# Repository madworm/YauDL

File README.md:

YauDL
=====

LAYOUT FILES: (Y)et (a)nother (u)seless (D)ummy (L)oad

For testing various projects I desire an adjustable constant current sink.
Nothing fancy, not microcontroller controlled, not 'constant power', maybe
with a display, maybe just use a DMM for that. BUT I need AMPS!
I'm shooting for a device that is capable to sink 5A. At least for a limited
amount of time, a couple of minutes should be enough to see if the DUT
overheats and/or craps out.

It will be as simple as can be: MOSFET(s), heatsink, sense resistor(s),
opamp(s), gain control, reference voltage, multi-turn pot to set the
reference current. It may or may not come with binding posts.

The first opamp will amplify the voltage drop on the mOhm range sense resistor
to a useful value (1V --> 1A), the second opamp will be wired in the usual
follower setup driving the MOSFET(s). I don't want to use a 1R sense resistor,
as this causes the device to need at least 5V for 5A. I'm aiming at something
lower.

BTW. It is strictly for DC input voltages.

---

Before having PC-boards made, please make sure you know about your manufacturer's peculiarities!
Especially drill-sizes and their tolerances may vary too much and give you trouble.

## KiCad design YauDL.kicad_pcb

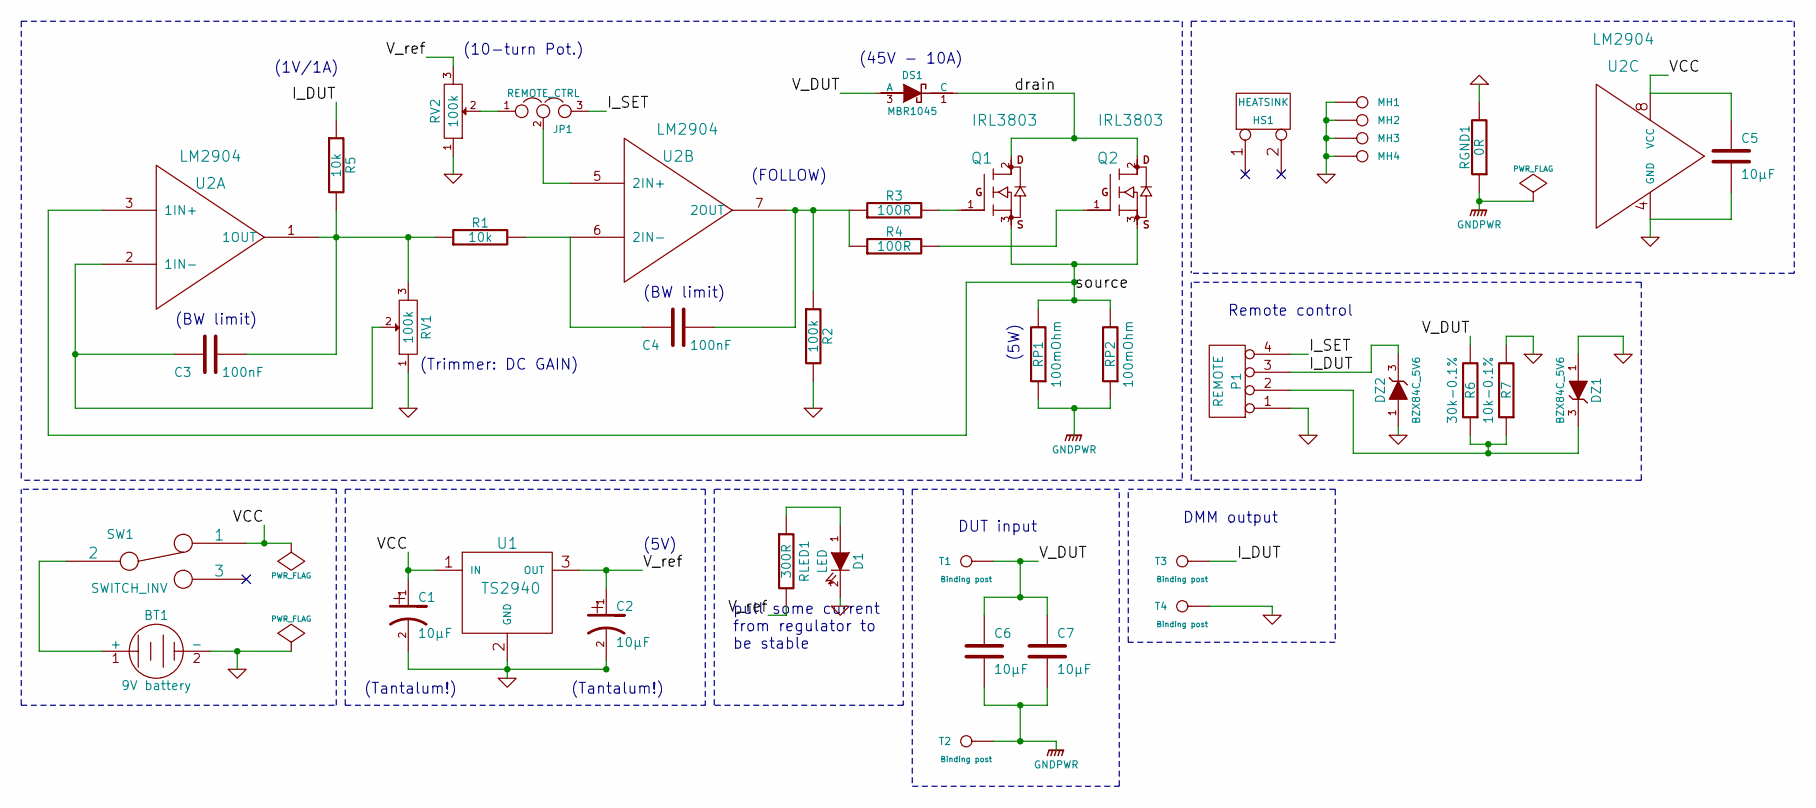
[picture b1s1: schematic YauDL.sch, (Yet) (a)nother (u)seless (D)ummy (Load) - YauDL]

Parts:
BT1: 9V battery
C1, C2, C5, C6, C7: 10µF
C3, C4: 100nF
D1: LED
DS1: MBR1045
DZ1, DZ2: BZX84C_5V6
HS1: HEATSINK
JP1: REMOTE_CTRL
MH1, MH2, MH3, MH4: CONN_1
P1: REMOTE
Q1, Q2: IRL3803
R1, R5: 10k
R2: 100k
R3, R4: 100R
R6: 30k-0.1%
R7: 10k-0.1%
RGND1: 0R
RLED1: 300R
RP1, RP2: 100mOhm
RV1, RV2: 100k
SW1: SWITCH_INV
T1, T2, T3, T4: Binding post
U1: TS2940
U2: LM2904

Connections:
/I_DUT: DZ2.3, P1.3, R5.1, T3.1
/I_SET: JP1.3, P1.4
/VCC: C1.1, C5.1, SW1.1, U1.1 (IN), U2.8 (VCC)
/V_DUT: C6.1, C7.1, DS1.3 (A), R6.2, T1.1
/V_ref: C2.1, RLED1.2, RV2.3, U1.3 (OUT)
/drain: DS1.1 (C), Q1.2 (D), Q2.2 (D)
/source: Q1.3 (S), Q2.3 (S), RP1.2, RP2.2, U2.3 (1IN+)
GND: BT1.2 (-), C1.2, C2.2, C5.2, D1.2 (K), DZ1.1, DZ2.1, MH1.1, MH2.1, MH3.1, MH4.1, P1.1, R2.2, R7.2, RGND1.2, RV1.1, RV2.1, T4.1, U1.2 (GND), U2.4 (GND)
GNDPWR: C6.2, C7.2, RGND1.1, RP1.1, RP2.1, T2.1
unnamed: D1.1 (A), RLED1.1
unnamed: C4.2, R2.1, R3.1, R4.1, U2.7 (2OUT)
unnamed: Q1.1 (G), R3.2
unnamed: C3.2, R1.1, R5.2, RV1.3, U2.1 (1OUT)
unnamed: C4.1, R1.2, U2.6 (2IN-)
unnamed: JP1.2, U2.5 (2IN+)
unnamed: BT1.1 (+), SW1.2
unnamed: JP1.1, RV2.2
unnamed: Q2.1 (G), R4.2
unnamed: DZ1.3, P1.2, R6.1, R7.1
unnamed: C3.1, RV1.2, U2.2 (1IN-)

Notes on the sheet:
Remote control
(45V - 10A)
pull some current from regulator to be stable
(Tantalum!)
(BW limit)
(5W)
DMM output
(10-turn Pot.)
(5V)
(FOLLOW)
(Trimmer: DC GAIN)
(1V/1A)
DUT input

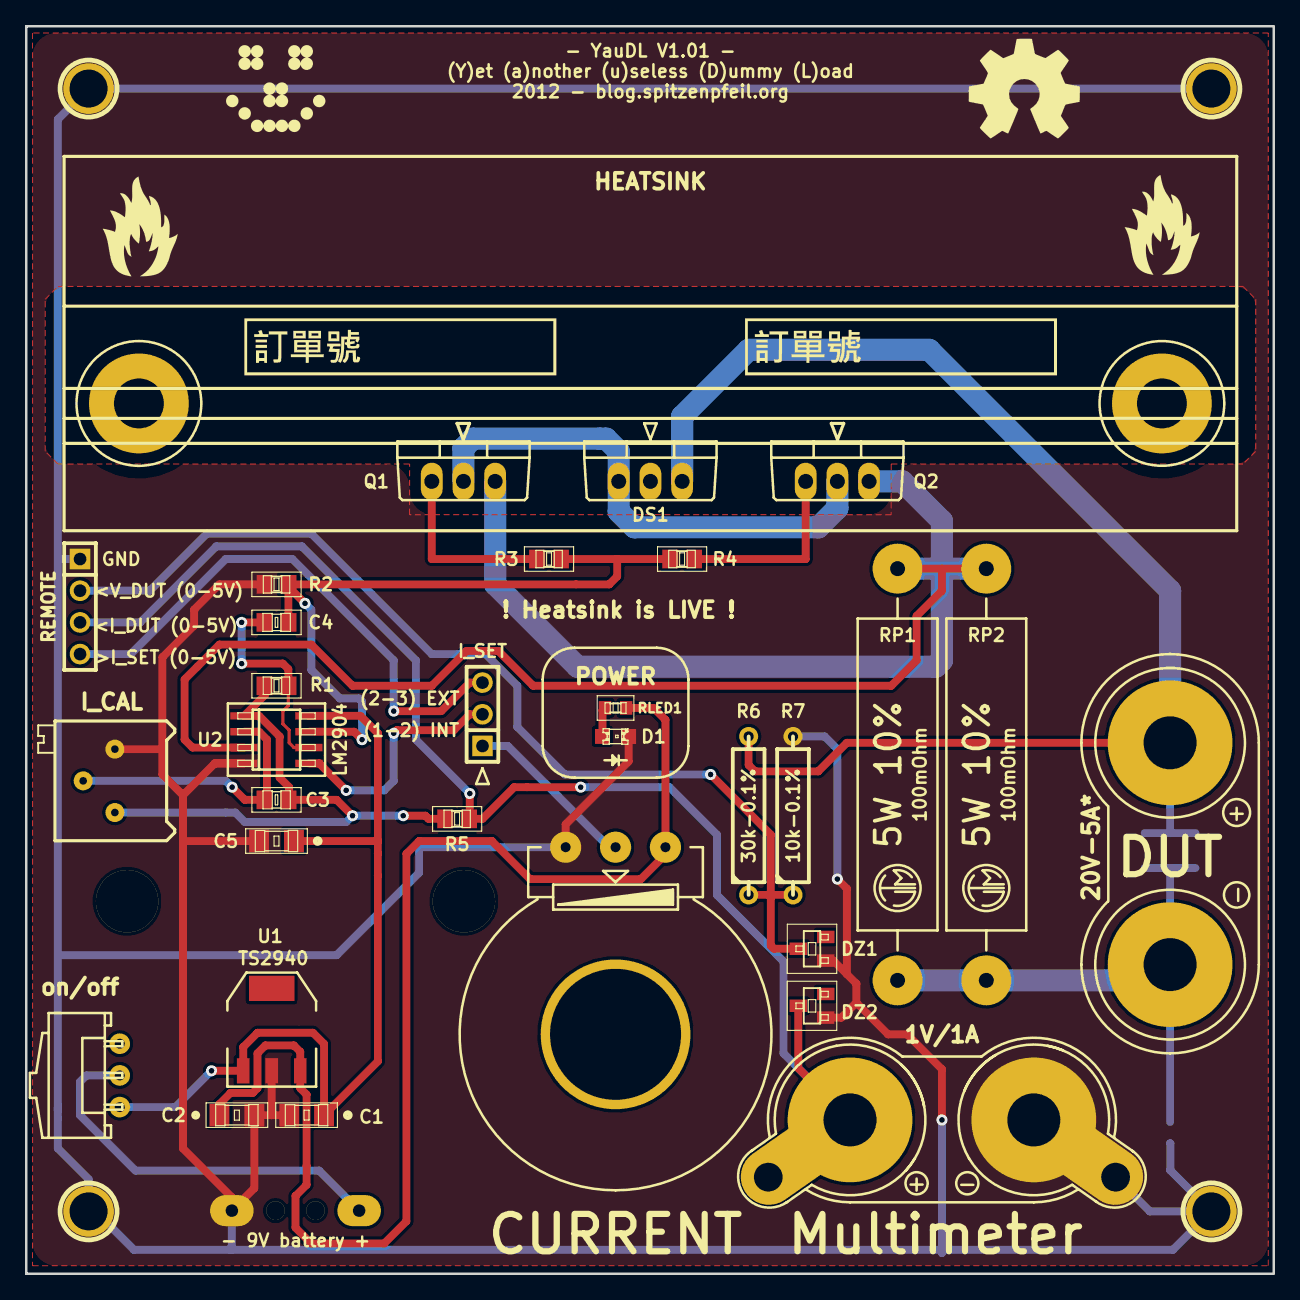
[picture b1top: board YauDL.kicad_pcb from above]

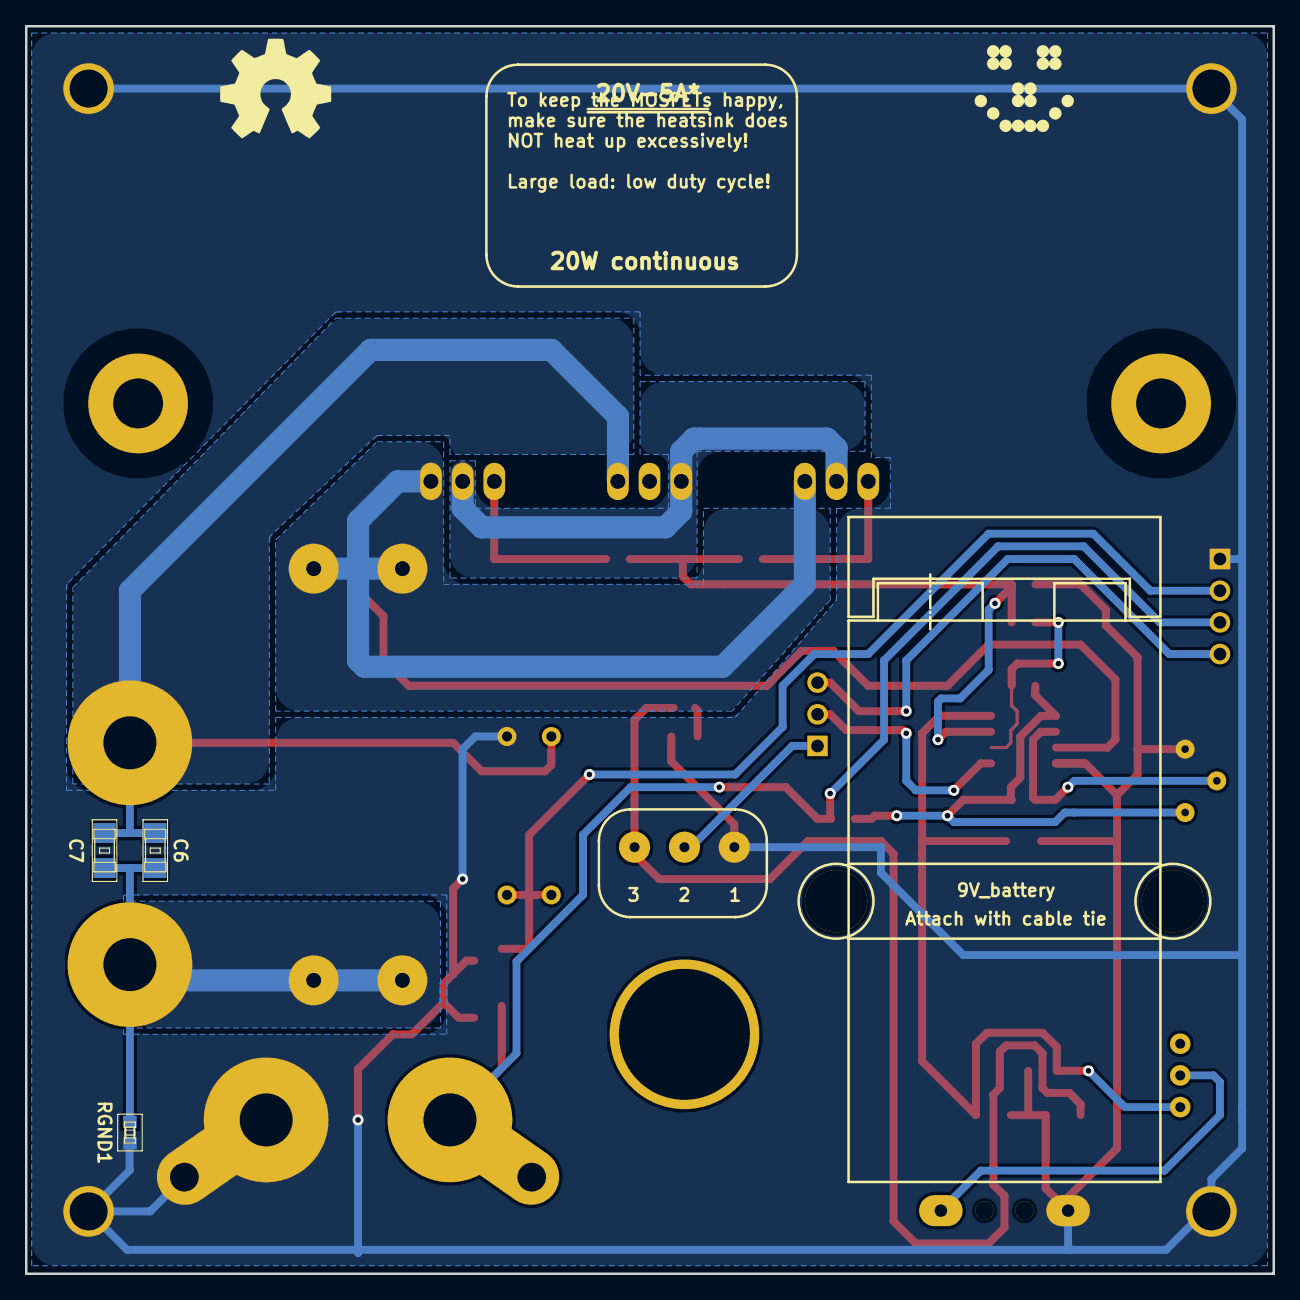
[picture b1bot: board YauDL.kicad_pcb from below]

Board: 2 copper layers, 100.0 x 100.0 mm, 49 parts (6 on the bottom side), 20 nets.

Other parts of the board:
G1, G2: LED_SMILE
G3, G4: OSHW_LOGO
G5, G6: FIRE
G7, G8: CHINESE_ORDER_NUMBER

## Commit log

2012-06-02 Fixed a typo.
2012-06-02 Added the github 'README.md' file.
2012-06-02 Added a preliminary BOM.
2012-06-02 First doodles.
2012-06-03 Schematic work.
2012-06-03 Doodles...
2012-06-04 Doodles.
2012-06-05 Doodle of doodles.
2012-06-05 Doooodle.
2012-06-05 Added a script to speed things up a bit.
2012-06-05 Done?
2012-06-05 Added a proper switch + footprint + calibration pot now flat on pcb.
2012-06-06 Tweaks.
2012-06-06 Sending this one out for review I guess.
2012-06-06 It is a 10.5mm mounting hole - not 10.6mm
2012-06-06 Switched to high-power resistors + added a RPP override shunt.
2012-06-07 Gate/source pins of the IRLZ34N were swapped ;-(
    Both the library and the footprint were wrong. Now I made my own.
    The IRLZ34N TO-220 (fullpack) has this pinout (front view, pins down):
    1 gate
    2 drain
    3 source
    The AO3401 P-MOSFET (SOT23) on the other hand has:
2012-06-07 Updated the BOM.
2012-06-08 Hiho hiho, I've found another Typo!
2012-06-09 Added a low-pass filter (RC=100ms) to the output opamp.
    LTSpice simulations indicated oscillation at higher currents.
    Hopefully the real thing doesn't require it, but I can bodge it.
2012-06-09 BOM updated. Now we're at V0.2 for both the schematic and the layout.
2012-06-09 Had to add some more caps and stuff. The PCB order will go into the trash.
2012-06-09 God some nasty oscillations on just one of my breadboards...
    Added another BW-limiting cap.
2012-06-11 New FET: IRL3803 TO-220 (150W dissip.) + some silkscreen tweaks.
2012-06-11 Added an image link to README.md
2012-06-11 Silkscreen tweaks regarding power input and duty cycle.
2012-06-12 Typo...
2012-06-13 Added 2x 10µF ceramic caps across the DUT input.
2012-06-14 Added another BOM. The information in there shall be hidden forever ;-)
2012-06-15 Silkscreen update.
2012-06-15 Some fixes:
    * The TS2940CW50 voltage regulatr NEEDS tantalum capacitors!
    * Changed the LED resistor to 470R to pull minimum current from
    regulator to make it stable. Otherwise it oscillates badly.
2012-06-15 V0.1 errata: back-to-back capacitors across DUT terminals.
2012-06-16 Addendum to the BOM.
2012-06-16 The MOSFETs need good cooling. The following is done to achieve it:
    * NO insulation of the TO-220 tabs that would impede heat transfer
    * Use thermal goop to improve things even more
    As the heatsink is now LIVE (up to 20V) and we don't want shorts
    * GND pour removed from underneath the heatsink's base + keepout
    * Added a warning to the top layer silkscreen
2012-06-16 Moved the MOSFETs closer together. Temperature should be equal.
2012-06-16 BOM fixed.
2012-06-17 RPP heats up when input voltage < 5V at high current. Fix needed.
2012-06-17 Added an inverting charge pump (TCM829).
    The reverse polarity protection using p-ch mosfets requires a
    minimum gate-source voltage for the fets to get a low enough
    R(ds)-on value. Otherwise they get HOT. By pulling the gate to
    -5V, V(gs) is sufficient even if the input voltage of the DUT
    is only a couple of volts (say 1-3V).
2012-06-17 Tweaks...
2012-06-17 Added the 'lithium cell' hack to ERRATA.txt
2012-06-17 Revert "Added the 'lithium cell' hack to ERRATA.txt"
    This reverts commit 2c432d9ca4af4951a4d6d5cf4995ad6059123f4f.
2012-06-17 Revert "Tweaks..."
    This reverts commit 0c1dc09ceebd5a01f0e86e24f0b4b3829b1a22fd.
2012-06-17 Revert "Added an inverting charge pump (TCM829)."
    This reverts commit de9563192d4ffa0c3c12e7bfe4f165a0f9cedcda.
2012-06-17 The on/off switch now switches VCC instead of GND. Silkscreen tweaks.
2012-06-17 Silkscreen tweaks.
2012-06-18 Added 2x 100R gate resistors for the power MOSFETs.
2012-06-18 Replaced the RPP with a beefy Schottky diode (MBR1045).
2012-06-18 Added the Schottky diode (MBR1045) to the V0.1 errata file.
2012-06-19 Updated the 'secret' BOM
2012-06-19 Moved binding posts a bit + added DMM probe holes.
2012-06-19 Dragon logo gone, OSHW logo instead.
2012-06-20 Added a dedicated area for 'factory text' on the PCB - in Chinese.
2012-06-20 Fixed the Chinese logo (crooked line).
2012-06-20 Updated the 'secret' BOM ;-)
2012-06-20 Increased the pad-size of the 25-turn trimmer a bit. It was too small.
2012-06-21 Added a remote-control option.
    * Header with: GND, I_DUT (0-5V out), V_DUT (0-5V out), I_SET (0-5V in)
    * Jumper to select between 'remote' and 'hand' operation
    * Voltage divider to scale 0-20 to 0-5V for V_DUT
    * 5.1V Zener diodes to limit output voltage of I_DUT and V_DUT
2012-06-21 Updated the BOM for V1.00
2012-06-21 Couldn't find any precision (0.1%) SMD resistors. Switched to DIP.
2012-06-21 Forgot to switch to through-hole for the 0.1% R in the BOM file.
2012-06-21 Forgot gerber update in '8fd0aff6de7db9c651f138ee2da098c7fb0b019b'.
2012-06-22 Moved C5 up a bit, so it doesn't get touched by the battery cable tie.
2012-06-24 Moved the BOM into a hybrid PDF file.
2012-07-02 Bugfixes for V1.00 --> V1.01
    * Moved the heatsink down about 0.5mm (20mil)
    * Moved the remote ctrl jumper, so it doesn't collide with the battery
    * Moved C5, so it doesn't interfere with the battery's cable tie
2012-07-02 Forgot to move the Chinese logos.
2012-07-02 Added V1.00 data to the errata file.
2012-07-02 V1.00 errata updates.
2012-07-05 Bugfixes to the schematic / BOM.
    * Changed RLED1 to 300R to pull more current. This should make the
    V-Reg. stable. Can't have 20mV oscillations on the output.
    * Changed the Zener diodes to 5V6 ones. With the sub 1mA current
    going through the precision voltage divider (R6/R7) these may
    finally clip at 5V - and not at 4.5V.
2012-07-06 Updated the ERRATA file with information about the 5V6 Zener diodes.
2012-09-03 Updated .gitignore
2013-01-23 Increased drill size for pin-headers to 40mil.
    Did NOT recreate gerber files!
2013-01-24 Recreated the gerber files (40mil drill size issue).
2013-02-11 Increased annular ring for pin-headers.
2013-05-14 Updated 'README.md'
2013-05-30 Updated BOM pdf-file.
2013-06-27 Converted to new kicad board format.
2013-09-13 Updated 'README.md'.
2013-09-17 Fixed missing module definitions (pcbnew BZR 4319 was barfing).
2015-04-27 Fixed vertical offset of multi-line-text.
    Some time ago KiCad changed how it handles that.
